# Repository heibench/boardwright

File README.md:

# boardwright

**Generate and edit KiCad boards and schematics from a short Python description,
checked by KiCad itself.**

> **Status: alpha.** It makes real, routed, DRC-clean KiCad 10 projects and edits
> existing ones in place. None of the example boards has been fabricated. The
> command line is the stable surface; the Python modules will move.

```sh
pip install boardwright             # add [live] to edit the board open in KiCad
boardwright doctor                  # what this machine has for each step
```

Needs KiCad 10 (its libraries and `kicad-cli`) and [Freerouting](https://github.com/freerouting/freerouting)
for autorouting. `boardwright doctor` finds them in the usual install places, Flatpak
included, and names the setting to use when it cannot.

## What it does

A board is a directory with a `board.py`: the circuit, where the parts go, and what
matters about the layout.

```python
from boardwright.circuit import Circuit

NAME, W, H = "ldo_breakout", 30, 20
CIRCUIT = c = Circuit("LDO breakout")
c.add("J1", "Connector_Generic:Conn_01x02", "VIN", "Connector_PinHeader_2.54mm:PinHeader_1x02_P2.54mm_Vertical", {1: "VIN", 2: "GND"})
c.add("U1", "Regulator_Linear:AMS1117-3.3", "AMS1117-3.3", "Package_TO_SOT_SMD:SOT-223-3_TabPin2", {1: "GND", 2: "+3V3", 3: "VIN"})
c.add("C1", "Device:C", "10u", "Capacitor_SMD:C_0805_2012Metric", {1: "VIN", 2: "GND"})
# ...
PLACE = {"J1": (3, 8.7, 0), "C1": (8.5, 10, 90), "U1": (15, 10, 270)}
REVIEW = {"near": [("C1.1", "U1.3", 6.0)]}      # input capacitor within 6 mm of the input pin
```

```sh
boardwright place examples/boards/ldo_breakout    # placement + ratsnest preview, ~5 s, no KiCad
boardwright gen examples/boards/ldo_breakout      # schematic, board, routing, pours
boardwright check examples/boards/ldo_breakout    # KiCad: ERC, DRC + parity, netlist, gerbers, plots
boardwright verify examples/boards/ldo_breakout   # PASS / NOT DONE
```

`verify` passes only when KiCad reports **zero** ERC and DRC findings at every
severity, schematic parity included, KiCad's netlist equals the declared circuit,
the fab files exist, and the engineering review is clean.

The review exists because a zero DRC is not a good board. An autorouter will run a
signal through a power polygon and leave the halves joined by a thin trace, and KiCad
accepts it. `REVIEW` checks what a reviewer would: decoupler-to-pin distance,
routed path lengths and pair matching (vias counted), how far a signal runs with no
ground on the adjacent layer, ground vias beside signal vias, pour coverage and
whether each pour is still one piece, and current capacity per IPC-2221.

**Boards that already exist** are edited in place and nothing is regenerated:

```sh
boardwright existing MYPROJ info              # layers, nets, pours, preview; any size of board
boardwright existing MYPROJ review            # the same review, against a spec beside the board
boardwright existing MYPROJ apply             # REMOVE, MOVE, RIPUP, ROUTES, TRACKS, VIAS, ZONES from the spec
boardwright existing MYPROJ reroute /SDA      # re-route named nets; every other net stays byte-identical
boardwright existing MYPROJ verify            # review + no DRC finding that is not in the baseline
boardwright sch MYPROJ set R12 Value=4k7      # one block of the schematic replaced, the rest untouched
boardwright live apply edit.py                # the same edits to the board open in KiCad, one undo step
```

## Exit codes

The same as the other [heibench](https://heibench.com/) tools, so a script or CI job can
branch on them:

| Code | Meaning |
|---|---|
| 0 | done: the board passed, or the edit was made |
| 1 | violated or refused: a finding about the design, or an edit not made |
| 2 | could not tell: a check could not be decided (a KiCad report is missing or stale) |
| 4 | environment fault: KiCad, a library or Freerouting missing or failing, or a file or folder it cannot read or write; never a verdict on the design |
| 64 | usage: bad arguments, or a spec naming parts, nets or layers that are not there |

## How it decides

- **KiCad is the judge.** Nothing is "done" on the tool's own arithmetic. Every
  generated board goes through `kicad-cli`, and edits to existing designs are compared
  against a baseline that KiCad produced. Connectivity before and after an edit is
  checked with [netspec](https://github.com/heibench/netspec).
- **Placement and hand copper are yours; the rest is routed.** Power loops, USB pairs and
  anything sensitive are drawn in `board.py` (`TRACKS`, `VIAS`, `ZONES`). Parts can be
  placed by intent: `pad_at(1, ("U1", 24), dy=-1.7)` puts a capacitor's pad 1.7 mm from
  pin 24. Freerouting does the remaining small signals, and a pad-to-pad router finishes
  what it leaves open.
- **Edits are plain data.** An edit to an existing board is an ordered list of
  operations in the board's own coordinates, checked against the board before it runs,
  so the same file can be applied to the file on disk or to KiCad's open board.

## Examples

`examples/boards/` has seven boards made with it; all but the library fixture follow a vendor
reference design:

| Board | Layers | What it exercises |
|---|---|---|
| `ldo_breakout` | 2 | the loop itself |
| `rp2040_min` | 2 | 0.4 mm QFN, USB-C, crystal, QSPI flash |
| `tps54202_buck` | 2 | a switching regulator's current loops, hand-routed power |
| `stm32f103_min` | 2 | 0.5 mm LQFP-48, bottom-side decoupling, USB pair |
| `esp32c3_min` | 2 | RF module with antenna keep-out, USB on the bottom layer |
| `stm32f103_4l` | 4 | inner ground planes, return-path and via review |
| `customlib_test` | 2 | parts from a library outside KiCad's stock set |

`examples/existing/` has specs for demo projects that ship with KiCad, for trying the
existing-board and schematic commands. [`docs/devlog/`](docs/devlog/) records what each
board broke in the tool and what was changed.

## Documentation

The site is at **https://heibench.com/boardwright/**. In this repository:

- [`docs/guide.md`](docs/guide.md): the full workflow, every `board.py` option, existing
  boards and schematics, the live KiCad client, and what the tool does badly.
- [`docs/devlog/gaps.md`](docs/devlog/gaps.md): known limits.
- [`skills/boardwright/SKILL.md`](skills/boardwright/SKILL.md): the agent skill, also
  installed with the package: `cd "$(boardwright --docs)"` and read
  `skills/boardwright/SKILL.md`.

## Known limits

- Freerouting is not repeatable on dense boards; the pad-to-pad router does not push
  other tracks aside, tune lengths or route pairs as pairs.
- Schematic editing changes fields, removes parts, and adds a part by copying one with
  the same symbol. It cannot add a symbol the sheet does not already use, and a
  schematic change is pushed to the board in KiCad.
- Generated schematics are one flat sheet.
- Impedance figures are closed-form (IPC-2141, about +-10 %); confirm with your fab.
- KiCad 10 only. The live client uses KiCad's IPC API, which is what KiCad 11 builds on.

## Development

```sh
just setup     # uv sync --all-extras
just check     # ruff
just test      # pytest; the full KiCad pipeline test skips where KiCad is absent
```

## License

Apache-2.0. The example boards are generated from KiCad's libraries, whose licence
(CC-BY-SA 4.0 with an exception for designs that use them) places no restriction on
the boards.

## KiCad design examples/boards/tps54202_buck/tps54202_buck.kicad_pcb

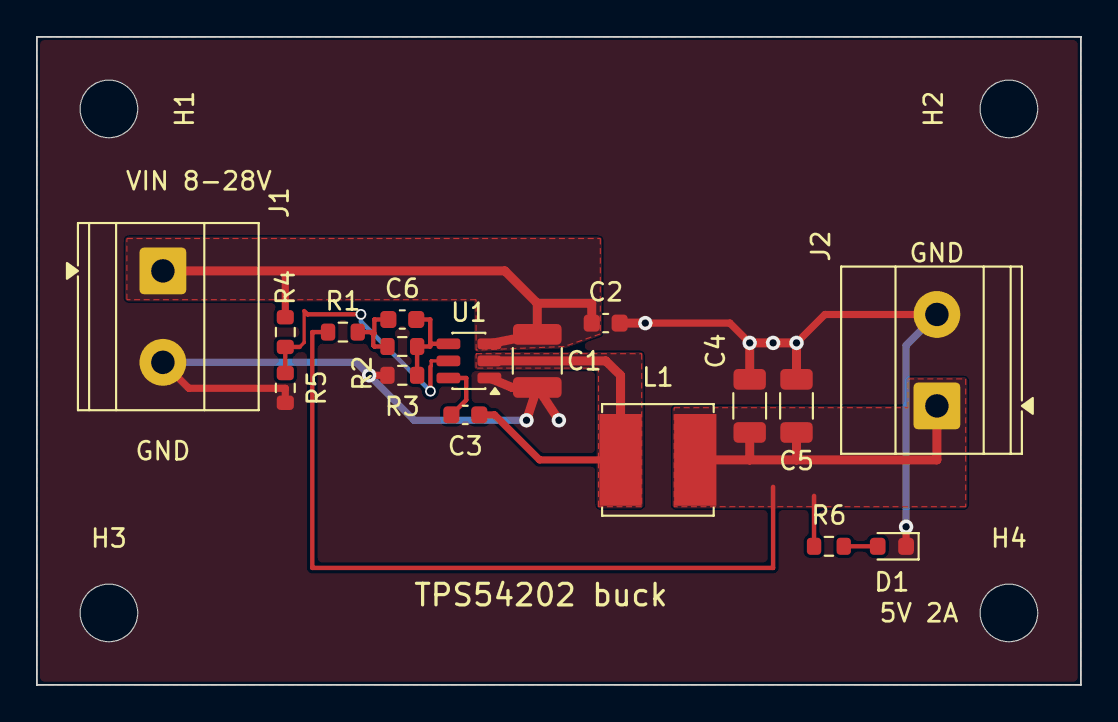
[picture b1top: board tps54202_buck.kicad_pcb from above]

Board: 2 copper layers, 58.0 x 36.0 mm, 21 parts (0 on the bottom side), 9 nets.

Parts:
C1: 10u 35V; C_1210_3225Metric
C2: 100n 50V; C_0603_1608Metric
C3: 100n; C_0603_1608Metric
C4, C5: 22u 16V; C_1206_3216Metric
C6: 75p; C_0603_1608Metric
D1: PWR; LED_0603_1608Metric
H1, H2, H3, H4: M3; MountingHole_3.2mm_M3
J1: VIN 8-28V; TerminalBlock_Phoenix_MKDS-1,5-2-5.08_1x02_P5.08mm_Horizont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
J2: VOUT 5V; TerminalBlock_Phoenix_MKDS-1,5-2-5.08_1x02_P5.08mm_Horizont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
L1: 15u 3A; L_Bourns_SRN6045TA
R1: 49.9; R_0603_1608Metric
R2: 100k; R_0603_1608Metric
R3: 13.3k; R_0603_1608Metric
R4: 511k; R_0603_1608Metric
R5: 105k; R_0603_1608Metric
R6: 2.2k; R_0603_1608Metric
U1: TPS54202; SOT-23-6

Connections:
BOOT: C3.1, U1.6
EN: R4.2, R5.1, U1.5
FB: C6.2, R2.2, R3.1, U1.4
GND: C1.2, C2.2, C4.2, C5.2, D1.1, J1.2, J2.2, R3.2, R5.2, U1.1
LED_A: D1.2, R6.2
SW: C3.2, L1.1, U1.2
VIN: C1.1, C2.1, J1.1, R4.1, U1.3
VOUT: C4.1, C5.1, J2.1, L1.2, R1.1, R6.1
VSENSE: C6.1, R1.2, R2.1

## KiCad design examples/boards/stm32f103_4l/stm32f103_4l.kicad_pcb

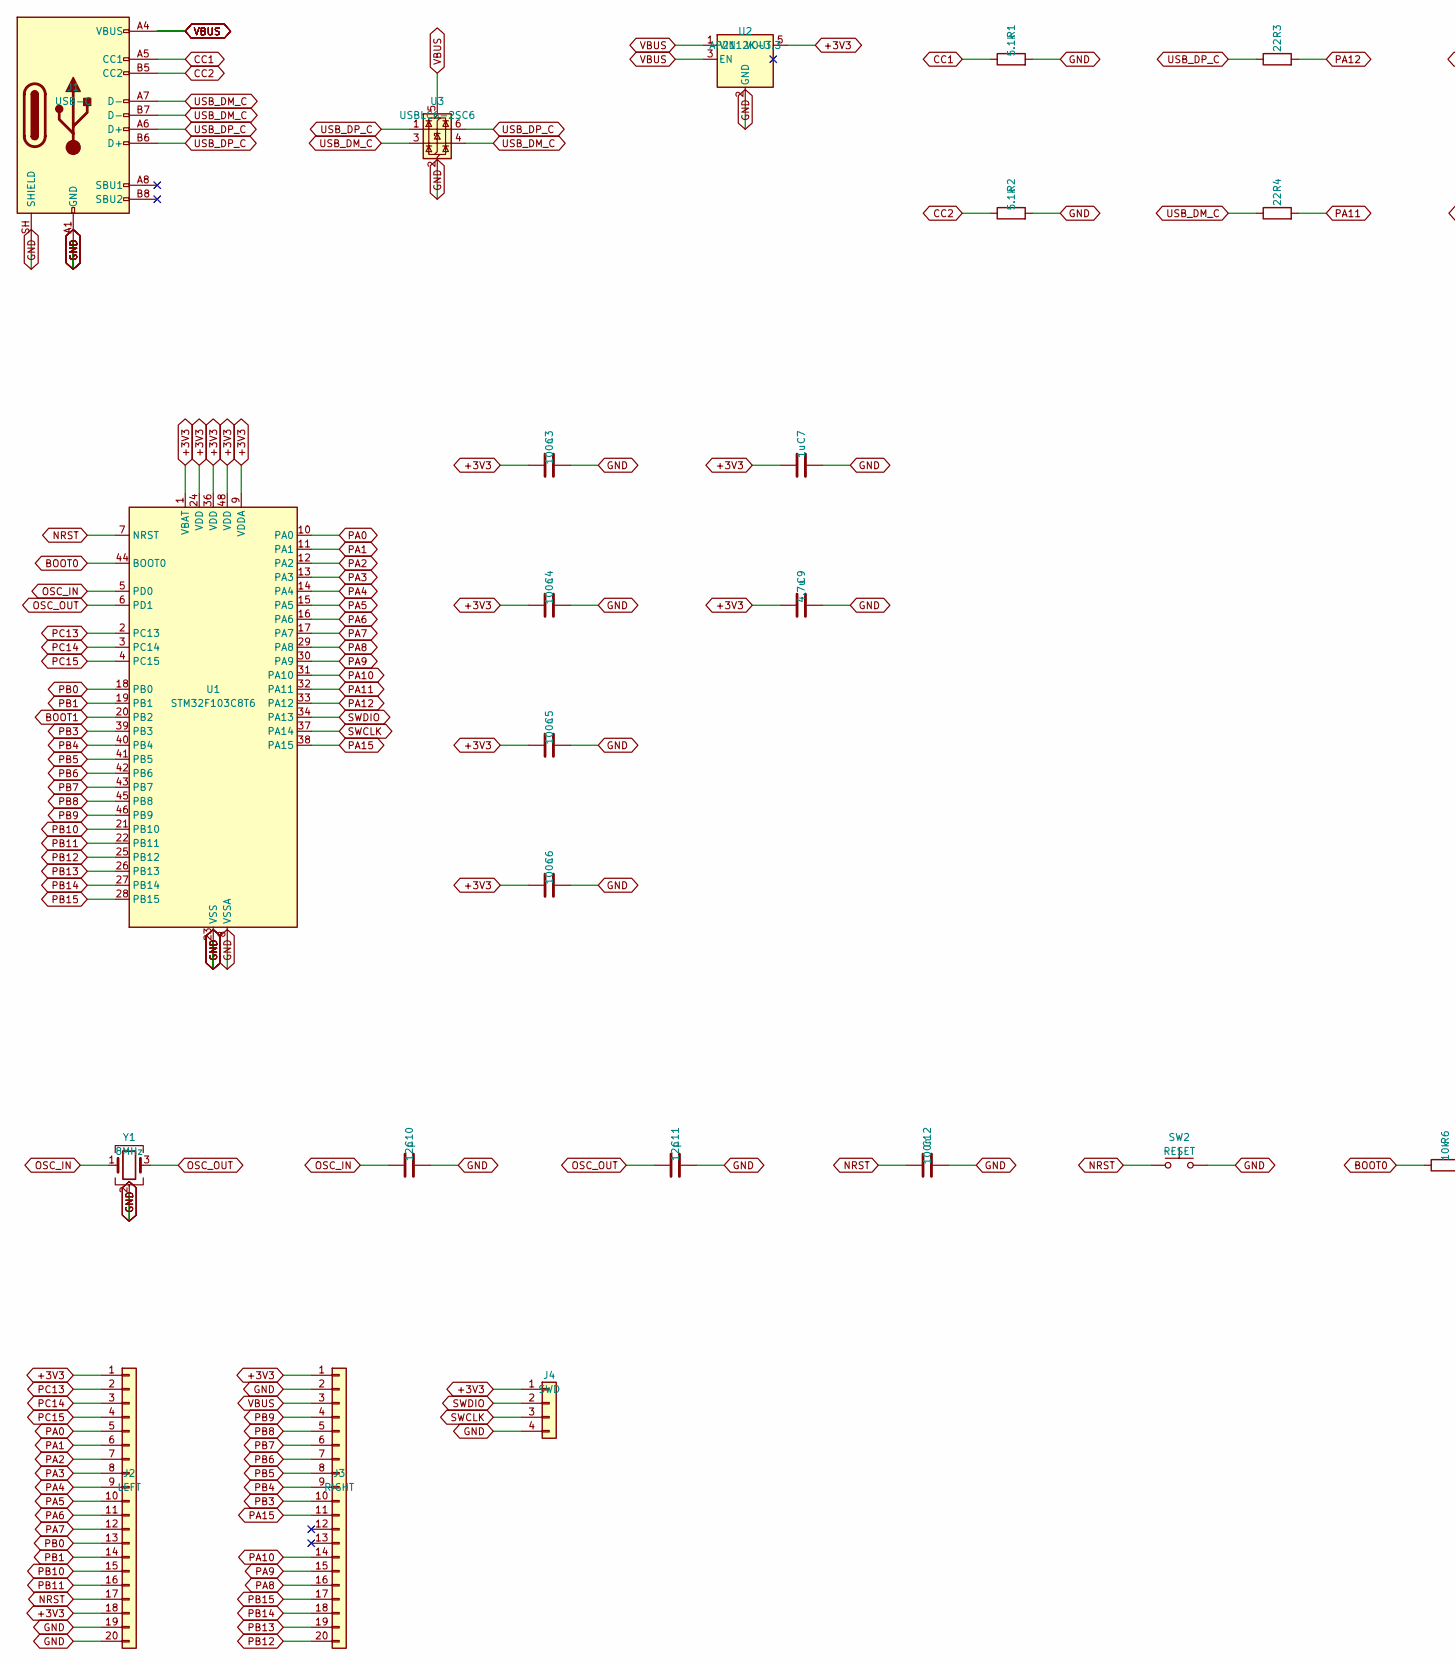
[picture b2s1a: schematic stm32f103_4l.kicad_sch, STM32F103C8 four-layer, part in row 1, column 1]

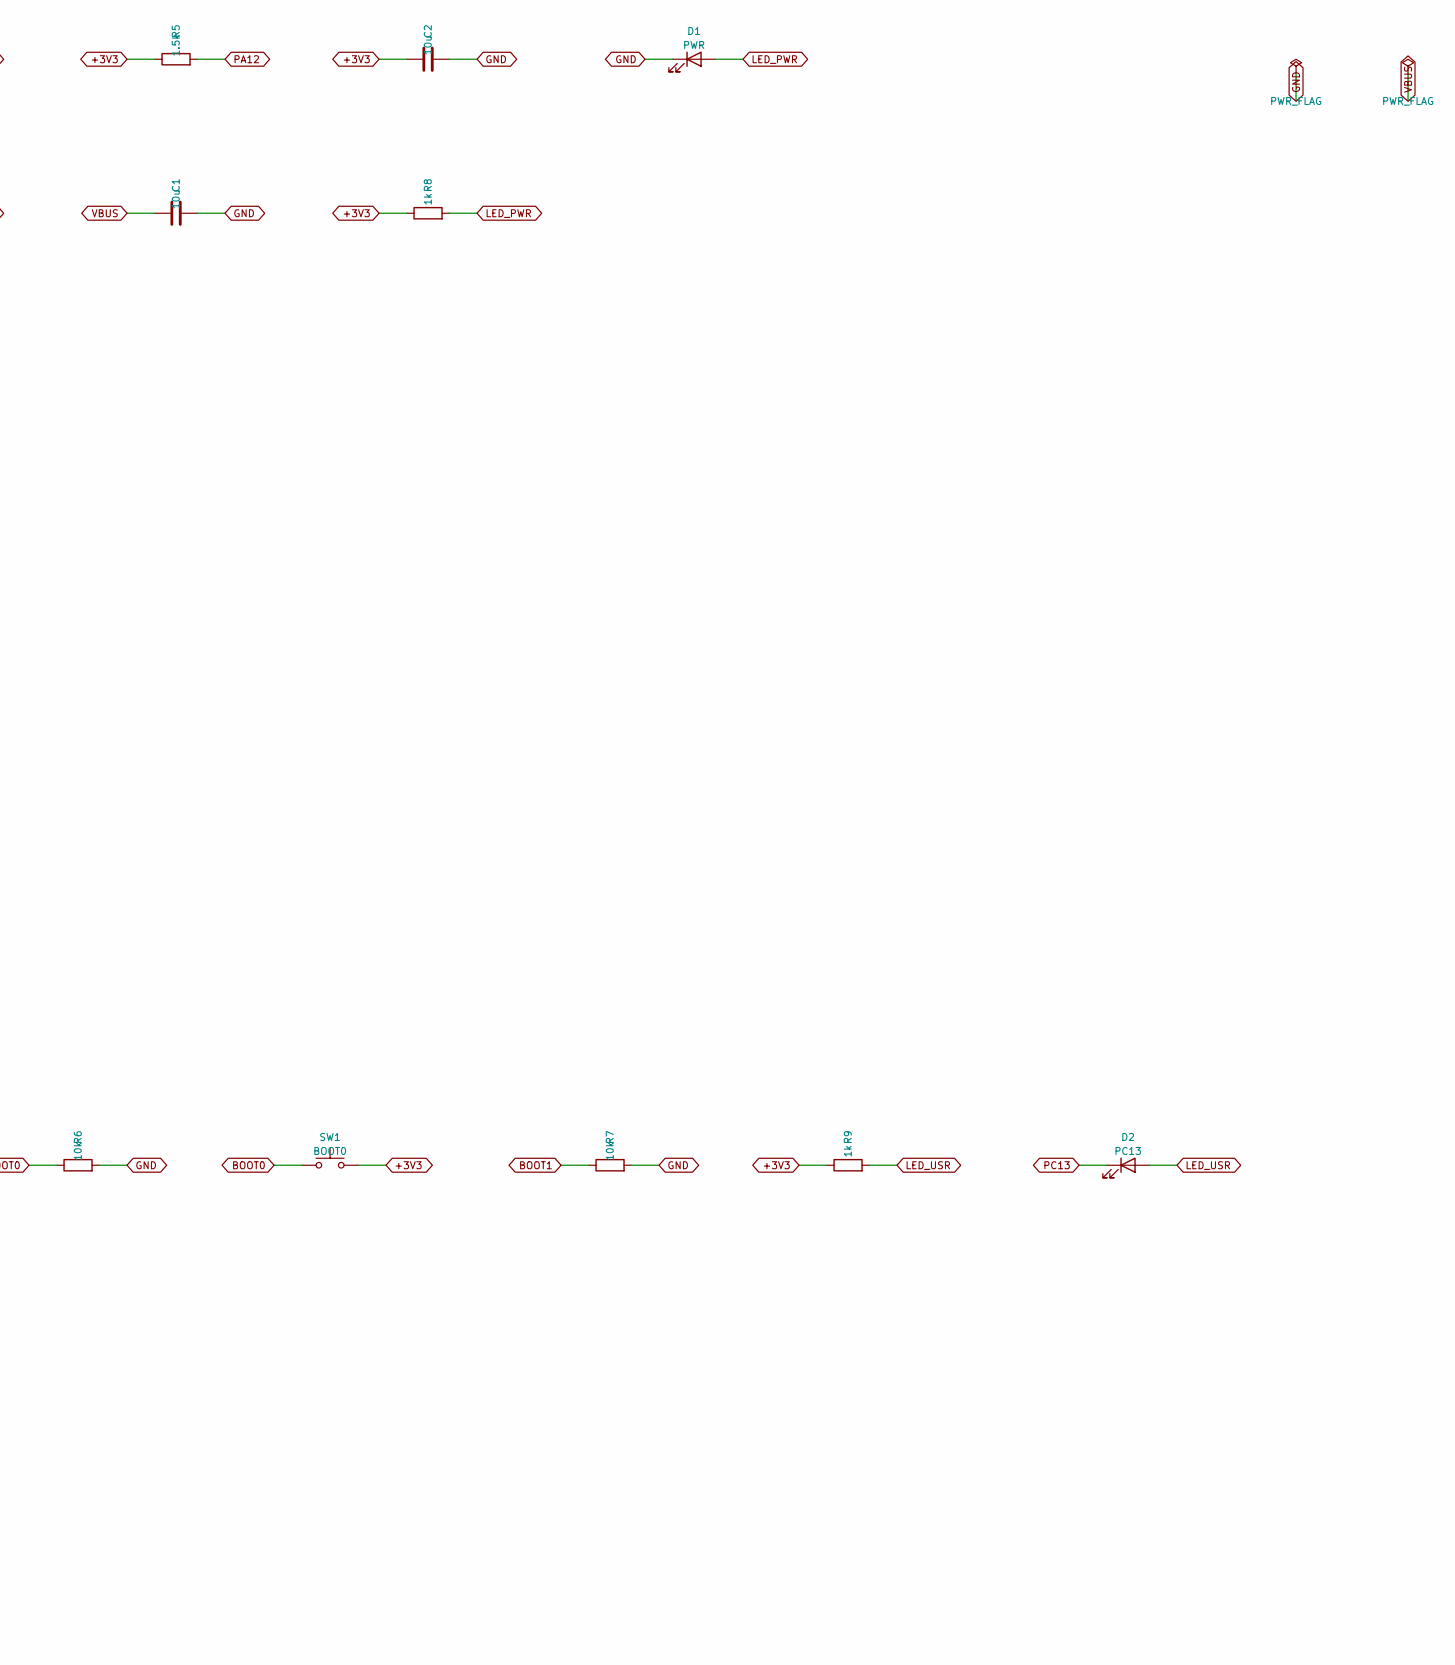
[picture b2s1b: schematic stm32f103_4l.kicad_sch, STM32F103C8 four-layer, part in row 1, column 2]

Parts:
C1, C2: 10u; C_0805_2012Metric
C3, C4, C5, C6, C12: 100n; C_0402_1005Metric
C7: 1u; C_0402_1005Metric
C9: 4.7u; C_0805_2012Metric
C10, C11: 12p; C_0402_1005Metric
D1: PWR; LED_0603_1608Metric
D2: PC13; LED_0603_1608Metric
J1: USB-C; USB_C_Receptacle_GCT_USB4105-xx-A_16P_TopMnt_Horizontal
J2: LEFT; PinHeader_1x20_P2.54mm_Vertical
J3: RIGHT; PinHeader_1x20_P2.54mm_Vertical
J4: SWD; PinHeader_1x04_P2.54mm_Vertical
R1, R2: 5.1k; R_0402_1005Metric
R3, R4: 22; R_0402_1005Metric
R5: 1.5k; R_0402_1005Metric
R6, R7: 10k; R_0402_1005Metric
R8, R9: 1k; R_0402_1005Metric
SW1: BOOT0; SW_SPST_EVQP0
SW2: RESET; SW_SPST_EVQP0
U1: STM32F103C8T6; LQFP-48_7x7mm_P0.5mm
U2: AP2112K-3.3; SOT-23-5
U3: USBLC6-2SC6; SOT-23-6
Y1: 8MHz; Crystal_SMD_3225-4Pin_3.2x2.5mm

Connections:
+3V3: C2.1, C3.1, C4.1, C5.1, C6.1, C7.1, C9.1, J2.1, J2.18, J3.1, J4.1, R5.1, R8.1, R9.1, SW1.2, U1.1 (VBAT), U1.9 (VDDA), U1.24 (VDD), U1.36 (VDD), U1.48 (VDD), U2.5 (VOUT)
BOOT0: R6.1, SW1.1, U1.44 (BOOT0)
BOOT1: R7.1, U1.20 (PB2)
CC1: J1.A5 (CC1), R1.1
CC2: J1.B5 (CC2), R2.1
LED_PWR: D1.2 (A), R8.2
LED_USR: D2.2 (A), R9.2
NRST: C12.1, J2.17, SW2.1, U1.7 (NRST)
OSC_IN: C10.1, U1.5 (PD0), Y1.1
OSC_OUT: C11.1, U1.6 (PD1), Y1.3
PA0: J2.5, U1.10 (PA0)
PA1: J2.6, U1.11 (PA1)
PA2: J2.7, U1.12 (PA2)
PA3: J2.8, U1.13 (PA3)
PA4: J2.9, U1.14 (PA4)
PA5: J2.10, U1.15 (PA5)
PA6: J2.11, U1.16 (PA6)
PA7: J2.12, U1.17 (PA7)
PA8: J3.16, U1.29 (PA8)
PA9: J3.15, U1.30 (PA9)
PA10: J3.14, U1.31 (PA10)
PA11: R4.2, U1.32 (PA11)
PA12: R3.2, R5.2, U1.33 (PA12)
PA15: J3.11, U1.38 (PA15)
PB0: J2.13, U1.18 (PB0)
PB1: J2.14, U1.19 (PB1)
PB3: J3.10, U1.39 (PB3)
PB4: J3.9, U1.40 (PB4)
PB5: J3.8, U1.41 (PB5)
PB6: J3.7, U1.42 (PB6)
PB7: J3.6, U1.43 (PB7)
PB8: J3.5, U1.45 (PB8)
PB9: J3.4, U1.46 (PB9)
PB10: J2.15, U1.21 (PB10)
PB11: J2.16, U1.22 (PB11)
PB12: J3.20, U1.25 (PB12)
PB13: J3.19, U1.26 (PB13)
PB14: J3.18, U1.27 (PB14)
PB15: J3.17, U1.28 (PB15)
PC13: D2.1 (K), J2.2, U1.2 (PC13)
PC14: J2.3, U1.3 (PC14)
PC15: J2.4, U1.4 (PC15)
SWCLK: J4.3, U1.37 (PA14)
SWDIO: J4.2, U1.34 (PA13)
USB_DM_C: J1.A7 (D-), J1.B7 (D-), R4.1, U3.3 (I/O2), U3.4 (I/O2)
USB_DP_C: J1.A6 (D+), J1.B6 (D+), R3.1, U3.1 (I/O1), U3.6 (I/O1)

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
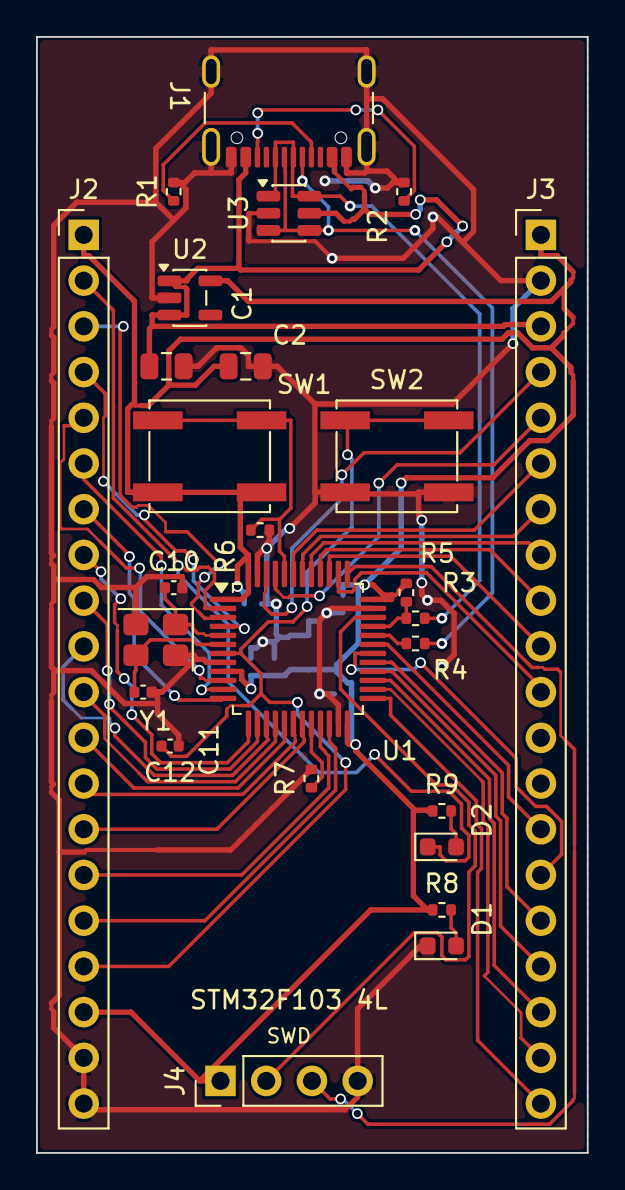
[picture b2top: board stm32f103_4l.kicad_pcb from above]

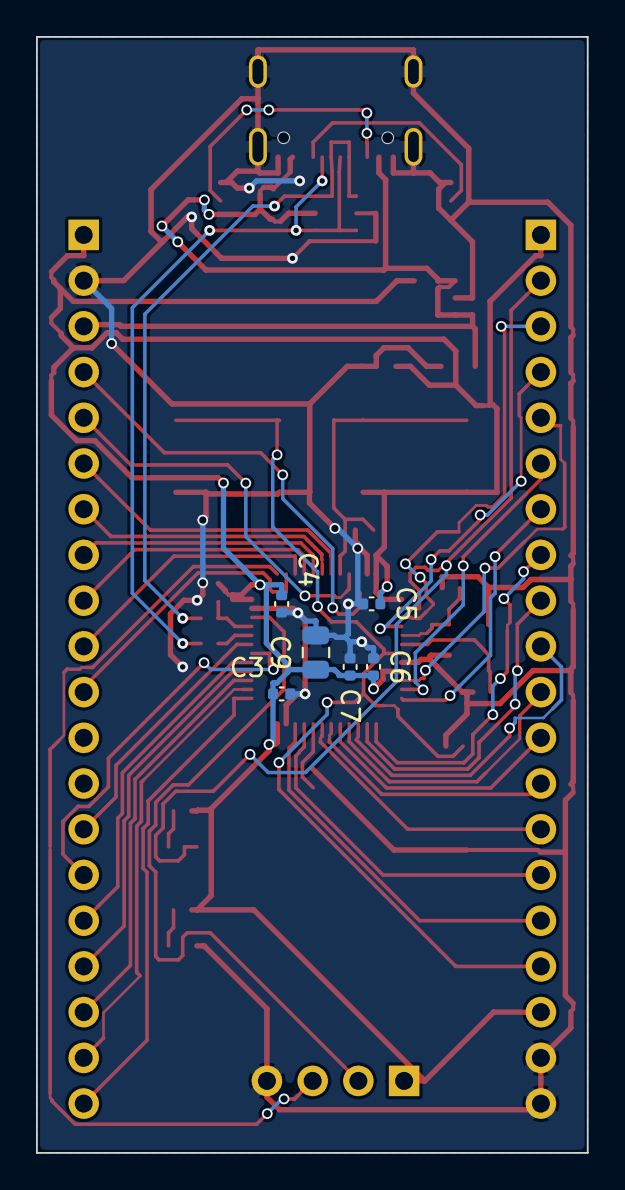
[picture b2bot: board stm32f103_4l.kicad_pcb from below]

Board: 4 copper layers, 30.6 x 62.0 mm, 32 parts (6 on the bottom side), 48 nets.

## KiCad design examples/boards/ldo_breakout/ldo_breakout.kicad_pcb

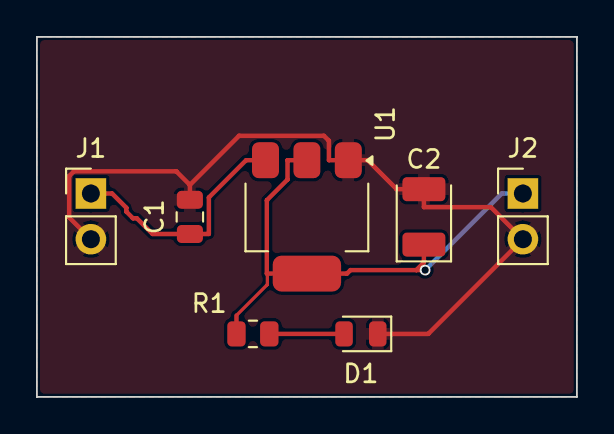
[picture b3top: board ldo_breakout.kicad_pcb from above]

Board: 2 copper layers, 30.0 x 20.0 mm, 7 parts (0 on the bottom side), 4 nets.

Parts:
C1: 10u; C_0805_2012Metric
C2: 22u tantalum; CP_EIA-3528-21_Kemet-B
D1: green; LED_0805_2012Metric
J1: VIN; PinHeader_1x02_P2.54mm_Vertical
J2: 3V3; PinHeader_1x02_P2.54mm_Vertical
R1: 1k; R_0805_2012Metric
U1: AMS1117-3.3; SOT-223-3_TabPin2

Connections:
+3V3: C2.1, J2.1, R1.1, U1.2
GND: C1.2, C2.2, D1.1, J1.2, J2.2, U1.1
LED_A: D1.2, R1.2
VIN: C1.1, J1.1, U1.3

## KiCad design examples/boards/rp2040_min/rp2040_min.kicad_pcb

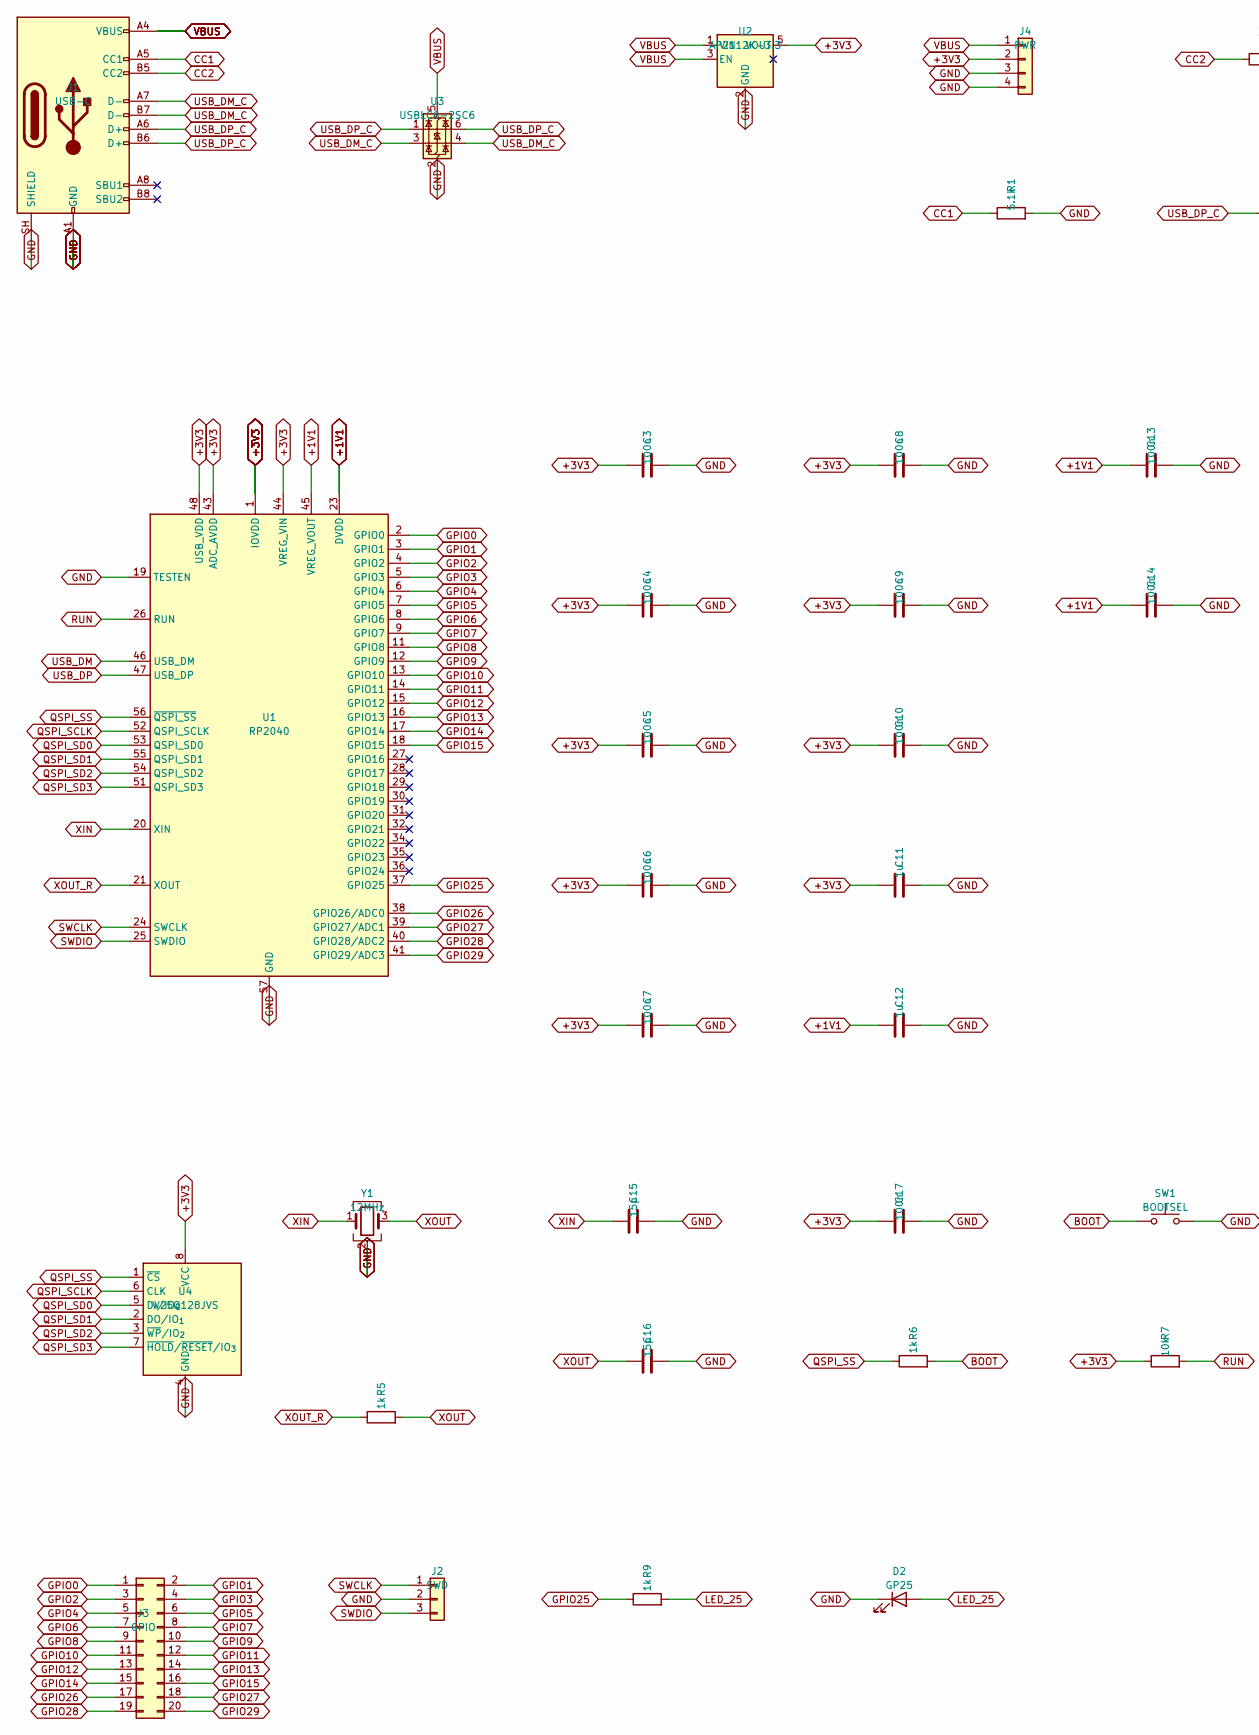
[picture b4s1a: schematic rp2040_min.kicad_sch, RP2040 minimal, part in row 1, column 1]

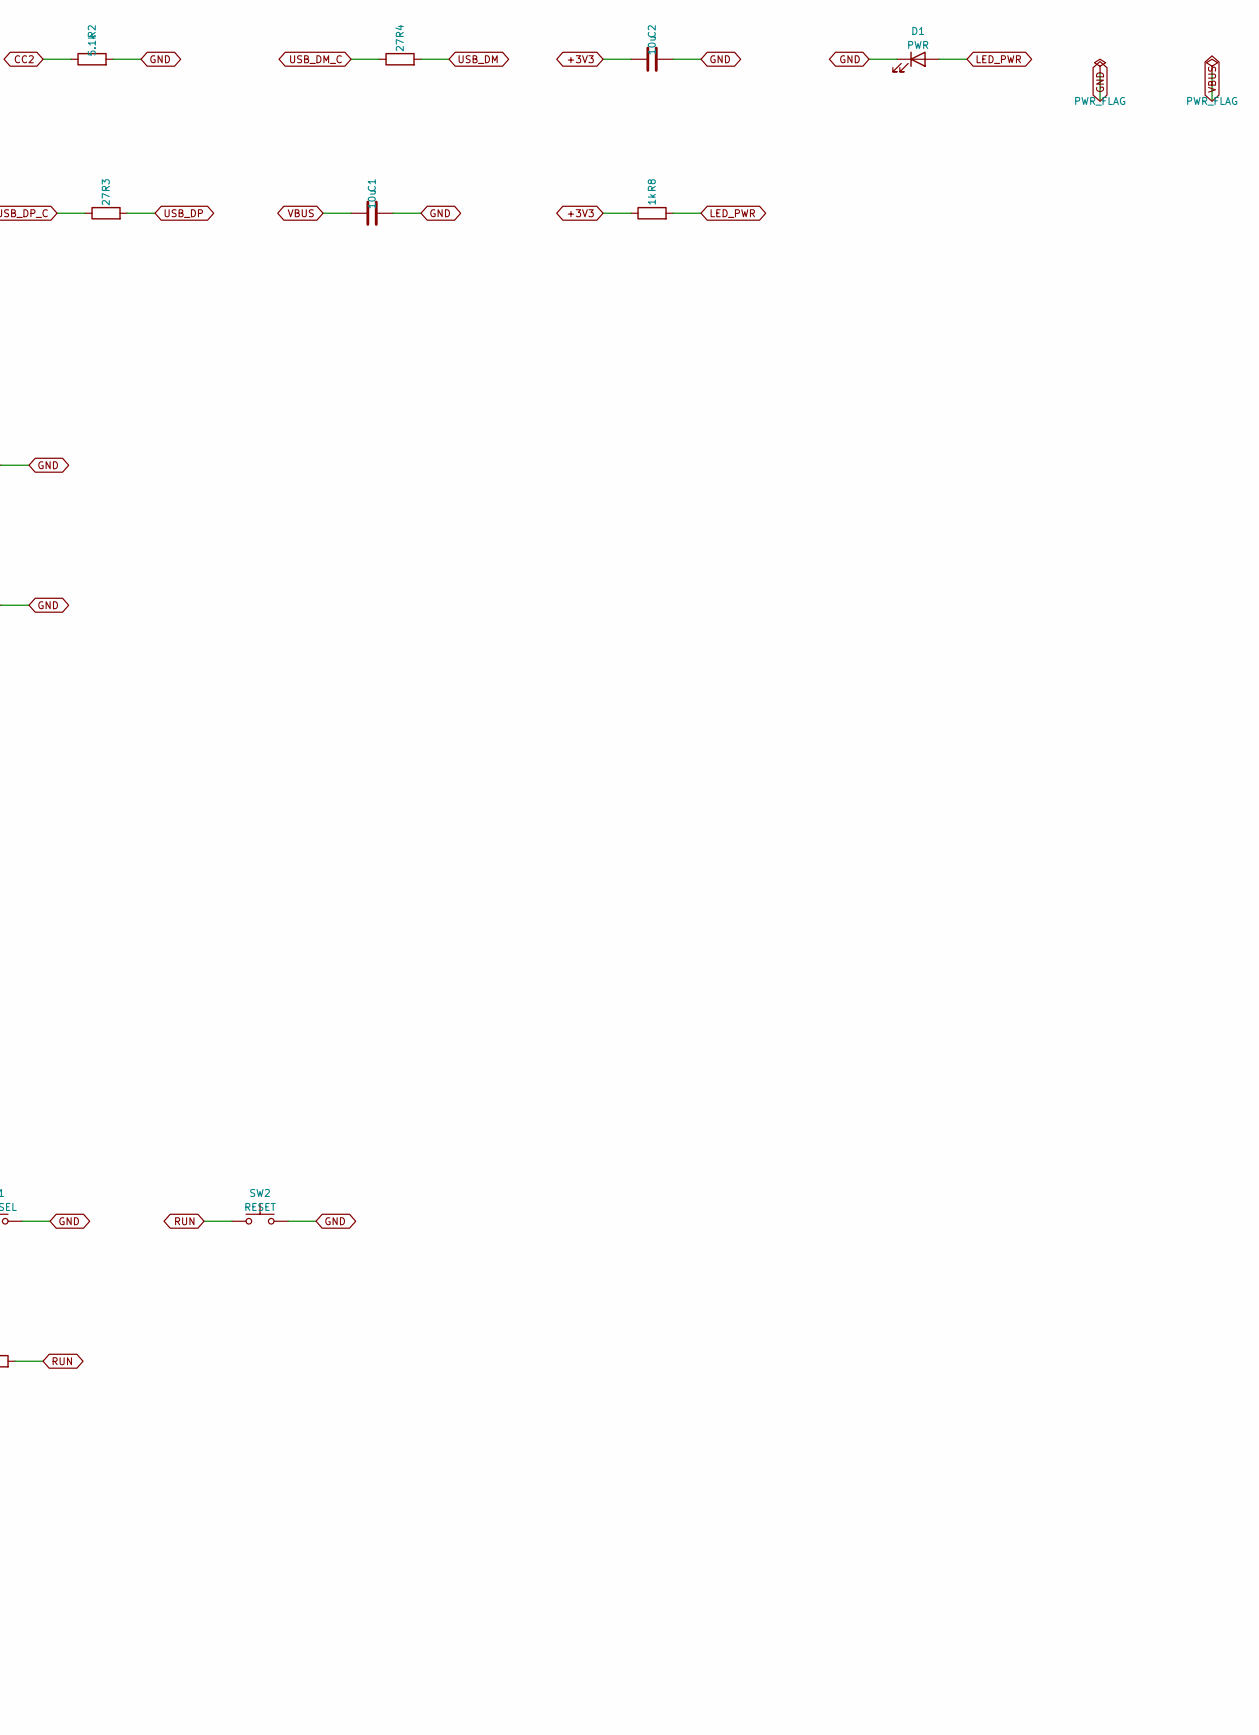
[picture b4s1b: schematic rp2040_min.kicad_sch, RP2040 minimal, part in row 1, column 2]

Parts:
C1, C2: 10u; C_0805_2012Metric
C3, C4, C5, C6, C7, C8, C9, C10, C13, C14, C17: 100n; C_0402_1005Metric
C11, C12: 1u; C_0402_1005Metric
C15, C16: 15p; C_0402_1005Metric
D1: PWR; LED_0603_1608Metric
D2: GP25; LED_0603_1608Metric
J1: USB-C; USB_C_Receptacle_GCT_USB4105-xx-A_16P_TopMnt_Horizontal
J2: SWD; PinHeader_1x03_P2.54mm_Vertical
J3: GPIO; PinHeader_2x10_P2.54mm_Vertical
J4: PWR; PinHeader_1x04_P2.54mm_Vertical
R1, R2: 5.1k; R_0402_1005Metric
R3, R4: 27; R_0402_1005Metric
R5, R6, R8, R9: 1k; R_0402_1005Metric
R7: 10k; R_0402_1005Metric
SW1: BOOTSEL; SW_SPST_EVQP0
SW2: RESET; SW_SPST_EVQP0
U1: RP2040; QFN-56-1EP_7x7mm_P0.4mm_EP3.2x3.2mm
U2: AP2112K-3.3; SOT-23-5
U3: USBLC6-2SC6; SOT-23-6
U4: W25Q128JVS; SOIC-8_5.3x5.3mm_P1.27mm
Y1: 12MHz; Crystal_SMD_3225-4Pin_3.2x2.5mm

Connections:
+1V1: C12.1, C13.1, C14.1, U1.23 (DVDD), U1.45 (VREG_VOUT), U1.50 (DVDD)
+3V3: C2.1, C3.1, C4.1, C5.1, C6.1, C7.1, C8.1, C9.1, C10.1, C11.1, C17.1, J4.2, R7.1, R8.1, U1.1 (IOVDD), U1.10 (IOVDD), U1.22 (IOVDD), U1.33 (IOVDD), U1.42 (IOVDD), U1.43 (ADC_AVDD), U1.44 (VREG_VIN), U1.48 (USB_VDD), U1.49 (IOVDD), U2.5 (VOUT), U4.8 (VCC)
BOOT: R6.2, SW1.1
CC1: J1.A5 (CC1), R1.1
CC2: J1.B5 (CC2), R2.1
GPIO0: J3.1, U1.2 (GPIO0)
GPIO1: J3.2, U1.3 (GPIO1)
GPIO2: J3.3, U1.4 (GPIO2)
GPIO3: J3.4, U1.5 (GPIO3)
GPIO4: J3.5, U1.6 (GPIO4)
GPIO5: J3.6, U1.7 (GPIO5)
GPIO6: J3.7, U1.8 (GPIO6)
GPIO7: J3.8, U1.9 (GPIO7)
GPIO8: J3.9, U1.11 (GPIO8)
GPIO9: J3.10, U1.12 (GPIO9)
GPIO10: J3.11, U1.13 (GPIO10)
GPIO11: J3.12, U1.14 (GPIO11)
GPIO12: J3.13, U1.15 (GPIO12)
GPIO13: J3.14, U1.16 (GPIO13)
GPIO14: J3.15, U1.17 (GPIO14)
GPIO15: J3.16, U1.18 (GPIO15)
GPIO25: R9.1, U1.37 (GPIO25)
GPIO26: J3.17, U1.38 (GPIO26/ADC0)
GPIO27: J3.18, U1.39 (GPIO27/ADC1)
GPIO28: J3.19, U1.40 (GPIO28/ADC2)
GPIO29: J3.20, U1.41 (GPIO29/ADC3)
LED_25: D2.2 (A), R9.2
LED_PWR: D1.2 (A), R8.2
QSPI_SCLK: U1.52 (QSPI_SCLK), U4.6 (CLK)
QSPI_SD0: U1.53 (QSPI_SD0), U4.5 (DI/IO_{0})
QSPI_SD1: U1.55 (QSPI_SD1), U4.2 (DO/IO_{1})
QSPI_SD2: U1.54 (QSPI_SD2), U4.3 (~WP/IO_{2})
QSPI_SD3: U1.51 (QSPI_SD3), U4.7 (~HOLD/~RESET/IO_{3})
QSPI_SS: R6.1, U1.56 (~QSPI_SS), U4.1 (~CS)
RUN: R7.2, SW2.1, U1.26 (RUN)
SWCLK: J2.1, U1.24 (SWCLK)
SWDIO: J2.3, U1.25 (SWDIO)
USB_DM: R4.2, U1.46 (USB_DM)
USB_DM_C: J1.A7 (D-), J1.B7 (D-), R4.1, U3.3 (I/O2), U3.4 (I/O2)
USB_DP: R3.2, U1.47 (USB_DP)
USB_DP_C: J1.A6 (D+), J1.B6 (D+), R3.1, U3.1 (I/O1), U3.6 (I/O1)
XIN: C15.1, U1.20 (XIN), Y1.1
XOUT: C16.1, R5.2, Y1.3
XOUT_R: R5.1, U1.21 (XOUT)

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
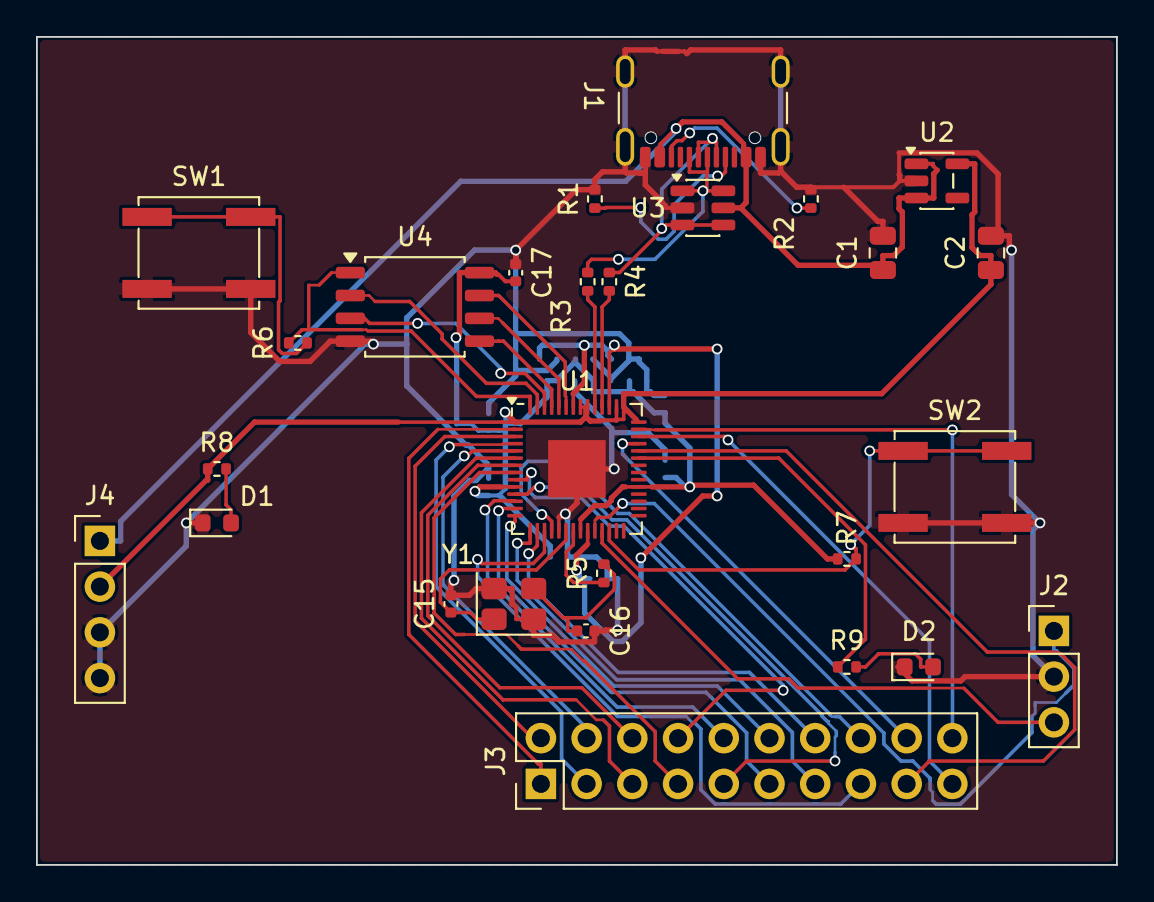
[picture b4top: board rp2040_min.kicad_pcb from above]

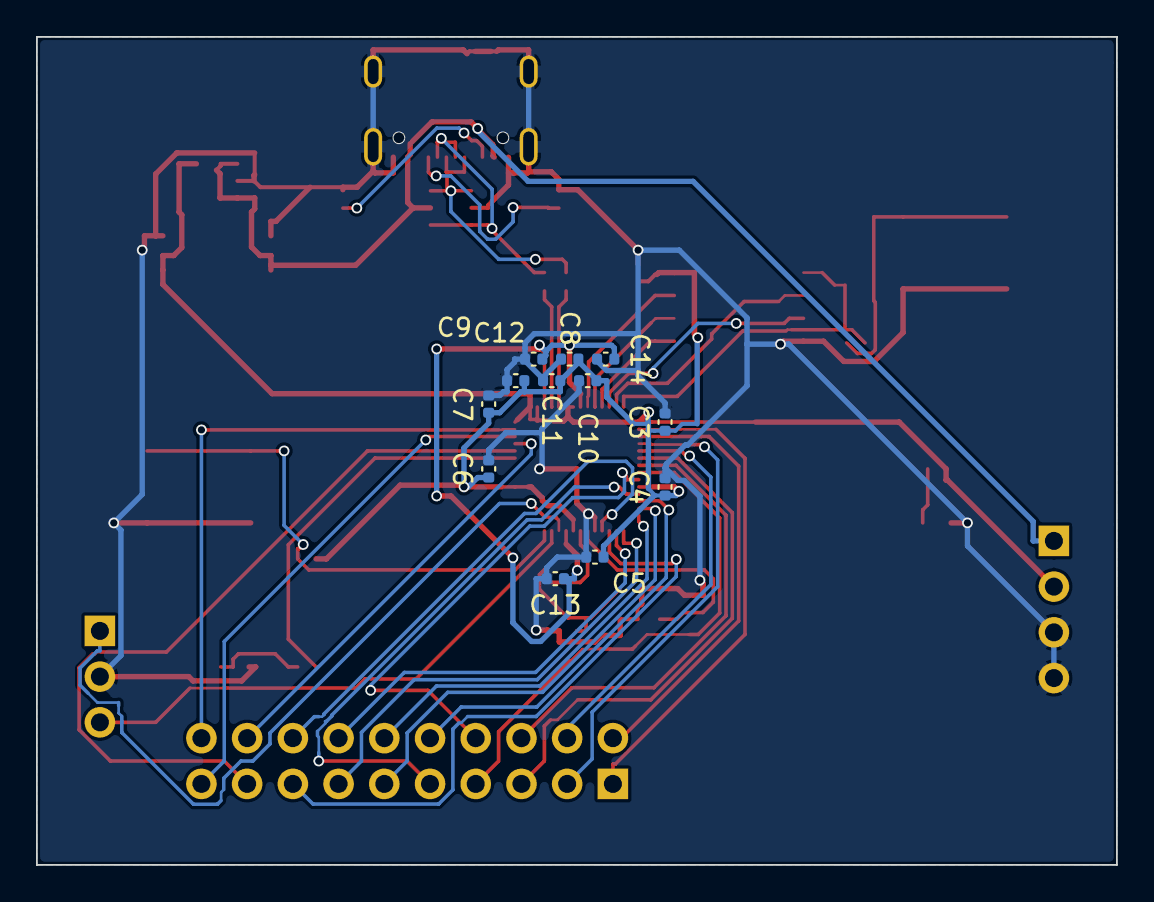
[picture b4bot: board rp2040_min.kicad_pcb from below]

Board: 2 copper layers, 60.0 x 46.0 mm, 39 parts (12 on the bottom side), 46 nets.
